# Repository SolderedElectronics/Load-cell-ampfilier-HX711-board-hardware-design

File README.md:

# Load-cell amplifier HX711 board Hardware Design

## About the Product

|  |
| :----------------------------------------------------------: |
| [Buy Load-cell amplifier HX711 board](https://www.solde.red/333005) |

The HX711 breakout allows you to easily read the weight value from a load-cell sensor (mass sensor). This small ADC is of great precision and is capable of measuring very small changes in the load-cell resistance, whose signals are amplified with the built-in amplifier. Subsequently, this same information is digitally transmitted to a microcontroller that simply converts the numbers obtained into the actual weight. That’s why this breakout is very useful for projects with scales or presence sensors, either for individuals or industry.

Breakout supports the connection of load cells that are made by the Wheatstone Bridge technique, like most of the load cells. They usually have four wires, two for power supply (E + and E, most often red and black), and two for signal (A + and A-, most commonly white and green wire). The pins for these wires are also indicated on the PCB and it is easy to connect.

---

## Repository Contents

This repository contains all design files for Load-cell amplifier HX711 board, organized as follows:

- **`CAD` folder**: Contains KiCAD design files, including:
  - Schematics
  - PCB layout
  - Panel PCB layout
  - Source 3D files in Fusion360, if any
  - All files are sorted by version with a detailed change log.
- **`OUTPUTS` folder**: Includes all production-ready files, such as:
  - Bill of Materials (BOM) and interactive BOM (iBOM)
  - PDF versions of schematics
  - 3D `.step` file of the board
  - 3D-printable models
  - Gerber files for PCB manufacturing
  - Image of the pinout of the board
  - Product image
  - Compliance, legal and generic sales documents

Refer to the `Change Log` in the CAD folder for details about updates between versions.

---

## Learn More About the Product

Beyond the repository, explore the following resources:

### Soldered Verify

The **Soldered Verify** system ensures every board you purchase from Soldered is fully functional. It also provides access to exclusive test data for your product. To get started, find the unique Soldered Verify ID on your product's packaging and enter the ID on the [Soldered Verify page](https://soldered.com/verify/) to access test results and additional product details.

### Soldered Community

Soldered Community is your go-to place for technical support. Our engineers track and answer all questions posted there, and it’s a great space for the maker community. Get answers to your questions and solutions for your challenges at [Soldered Community](https://soldered.com/community).

### solde.red

solde.red is an ultimate URL shortener and information hub. Access it by typing solde.red/ followed by your product SKU, e.g., [solde.red/333000](https://solde.red/333000), to find getting-started guides, datasheets, open-source hardware and software files, certifications, images, pinouts, and more. Read more about the shortener [here](https://solde.red/info/).

---

## Contributing

Contributions are welcome! Here’s how you can get involved:

- Submit pull requests to enhance the design or fix issues.
- Report bugs or problems by opening an issue.

We encourage community collaboration to make this product even better.

---

## About Soldered

[Soldered for Makers](https://soldered.com) specializes in designing and manufacturing electronic products tailored for enthusiasts, ranging from hobbyists to professionals. Our portfolio includes electronic boards, sensors, and actuators that are widely utilized in fields such as microelectronics, mechatronics, robotics, programming, and IoT. Every product we offer is designed in-house and built upon open-source hardware and software platforms. Proudly certified and manufactured within the European Union, our catalog likely includes the product you need for your project.

We complement these products with comprehensive tutorials and manuals, product descriptions, schematics, programming codes, and project examples. Our round-the-clock [customer and technical support](https://soldered.com/community) is available for all our products, irrespective of the sales channel. Soldered’s success and services reflect our maker community’s unwavering [trust](https://www.trustpilot.com/review/soldered.com), for which we are deeply grateful. Join our community and create using Soldered products.

---

## License

All Soldered open-source hardware (OSH) is under The TAPR Open Hardware License. Read more in the LICENSE file located in this repository.

**Disclaimer:**

No warranty - all designs in this repository are distributed in the hope that they will be useful, but without any warranty. They are provided "AS IS", therefore without warranty of any kind, either expressed or implied. The entire quality and performance of what you do with the contents of this repository are your responsibility. In no event Soldered Electronics will be liable for your damages, or losses, including any general, special, incidental, or consequential damage arising out of the use or inability to use the contents of this repository. 

---

## Have fun!

Thank you for your support from your fellow makers at Soldered Electronics.

Happy Making!

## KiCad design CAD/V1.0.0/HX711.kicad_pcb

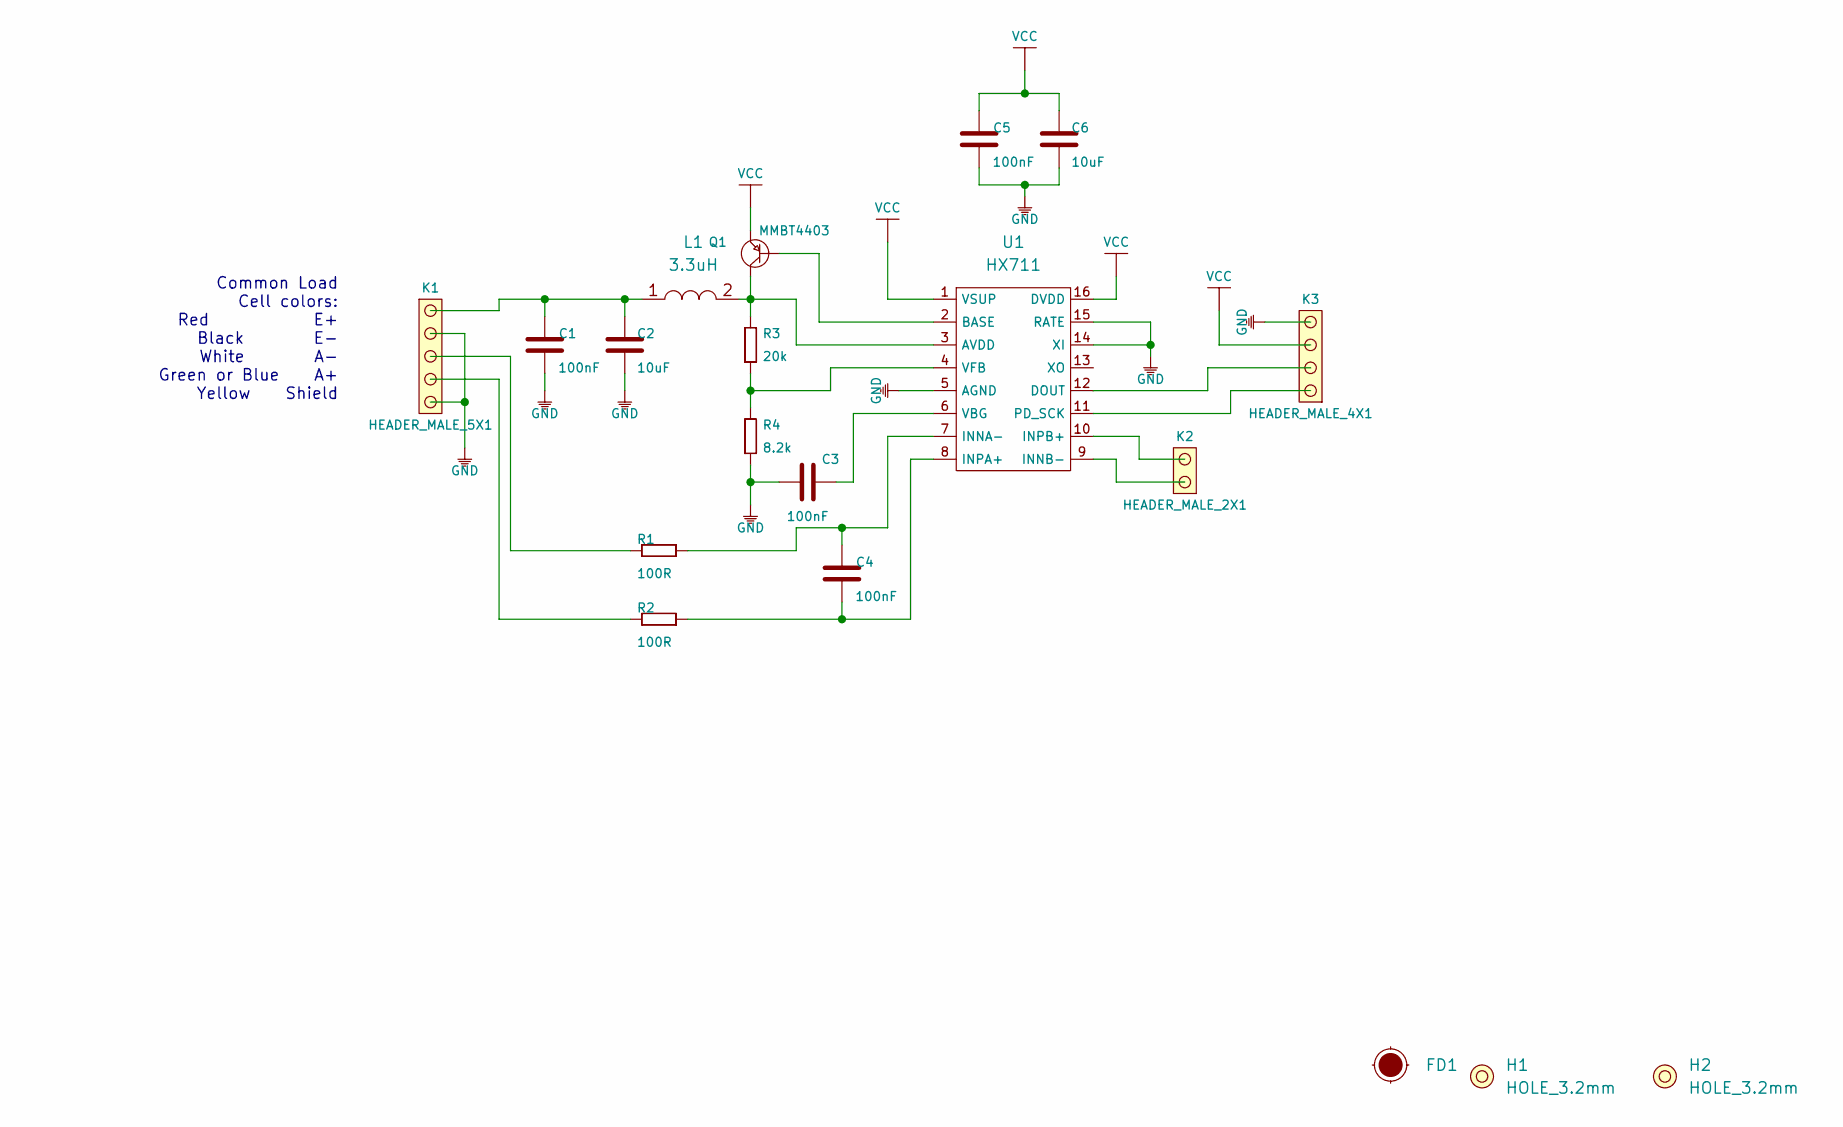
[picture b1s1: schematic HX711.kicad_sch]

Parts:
C1, C3, C4, C5: 100nF; 0603C
C2, C6: 10uF; 1206C
FD1: Fiducial_Stencil; FIDUCIAL_1MM_PASTE
H1, H2: HOLE_3.2mm
K1: HEADER_MALE_5X1
K2: HEADER_MALE_2X1
K3: HEADER_MALE_4X1
L1: 3.3uH; 0603L
Q1: MMBT4403; SOT-23-3
R1, R2: 100R; 0603R
R3: 20k; 0603R
R4: 8.2k; 0603R
U1: HX711; SOP-16

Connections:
GND: C1.1, C2.1, C3.1, C5.1, C6.1, K1.1, K1.4, K3.4, R4.1, U1.5 (AGND), U1.14 (XI), U1.15 (RATE)
unnamed: C1.2, C2.2, K1.5, L1.1
unnamed: C3.2, U1.6 (VBG)
unnamed: C4.1, R2.1, U1.8 (INPA+)
unnamed: C4.2, R1.1, U1.7 (INNA-)
unnamed: K1.2, R2.2
unnamed: K1.3, R1.2
unnamed: K2.1, U1.9 (INNB-)
unnamed: K2.2, U1.10 (INPB+)
unnamed: K3.1, U1.11 (PD_SCK)
unnamed: K3.2, U1.12 (DOUT)
unnamed: L1.2, Q1.3 (C), R3.2, U1.3 (AVDD)
unnamed: Q1.1 (B), U1.2 (BASE)
unnamed: R3.1, R4.2, U1.4 (VFB)
VCC: C5.2, C6.2, K3.3, Q1.2 (E), U1.1 (VSUP), U1.16 (DVDD)

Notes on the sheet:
Common Load Cell colors: Red E+ Black E- White A- Green or Blue A+ Yellow Shield

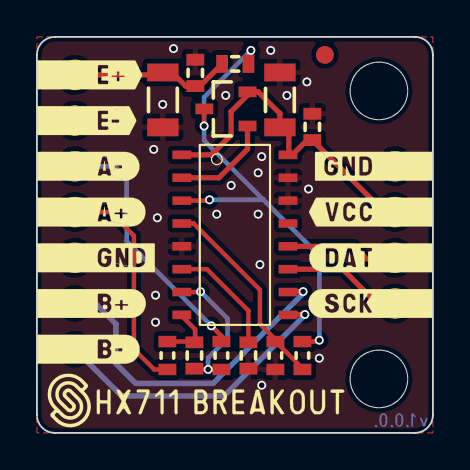
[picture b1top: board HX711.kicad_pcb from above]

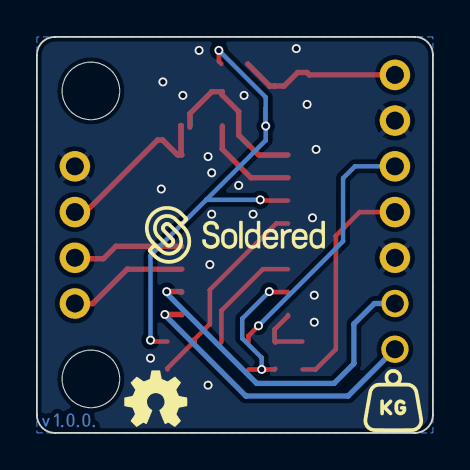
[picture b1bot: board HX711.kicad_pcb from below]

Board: 2 copper layers, 22.0 x 22.0 mm, 19 parts (3 on the bottom side), 15 nets.

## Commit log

2022-08-06 Updating open source files.
